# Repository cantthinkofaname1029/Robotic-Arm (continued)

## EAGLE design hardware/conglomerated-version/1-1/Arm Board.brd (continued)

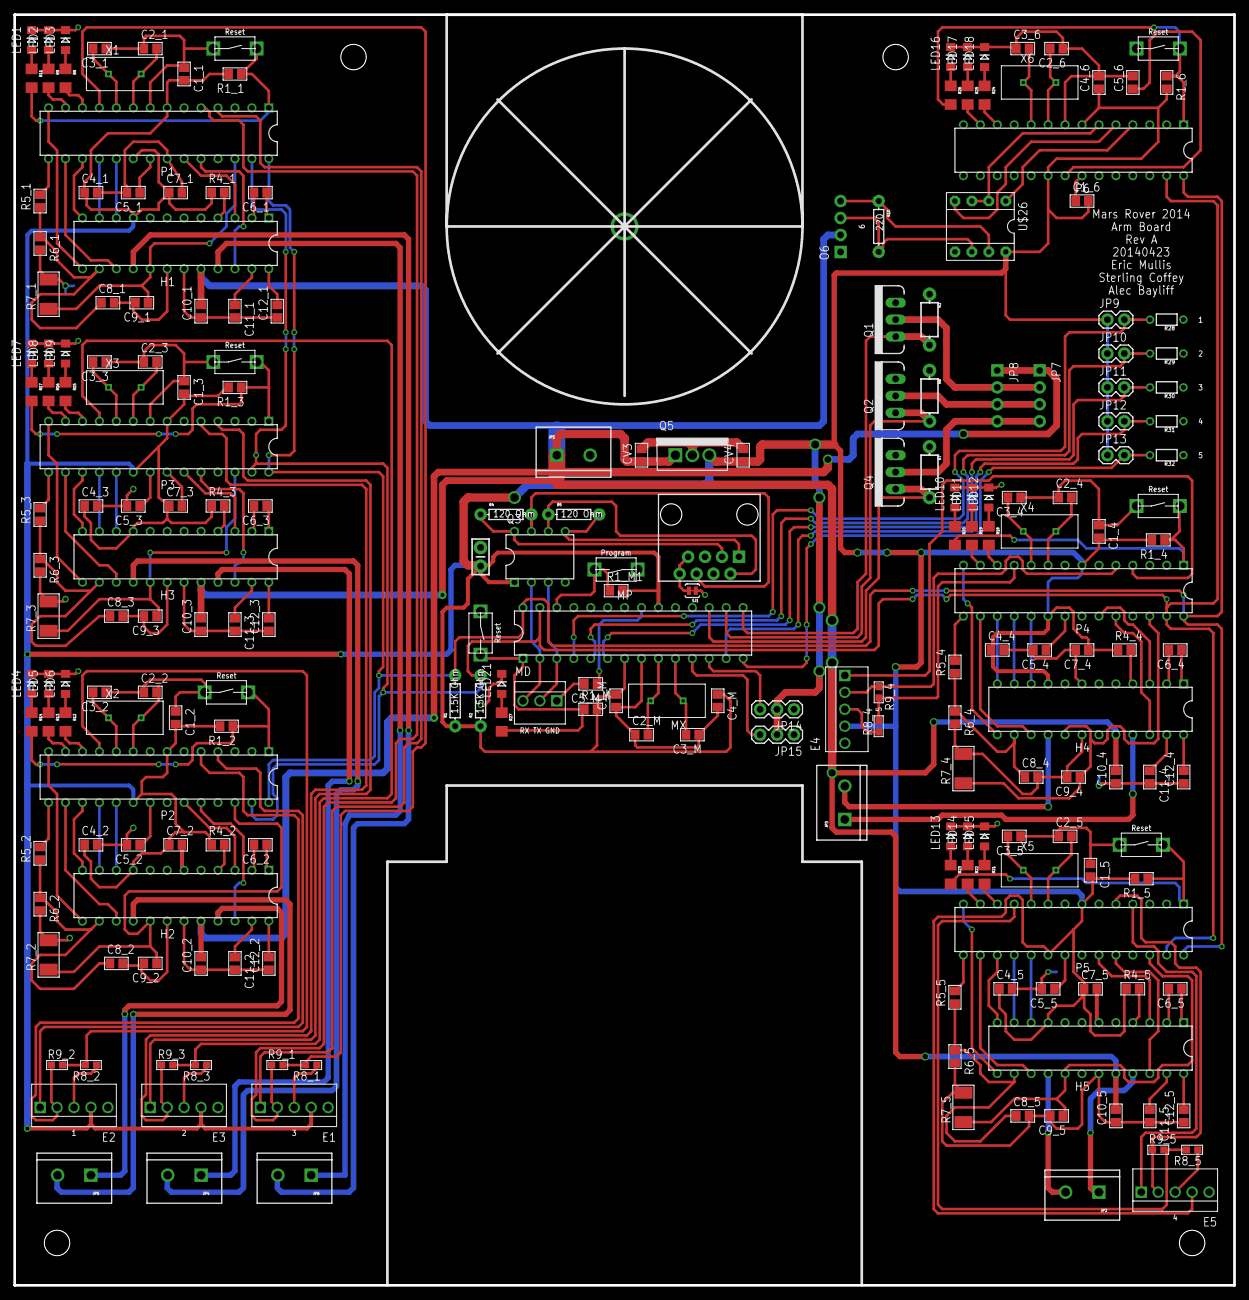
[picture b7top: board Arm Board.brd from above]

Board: 2 copper layers, 182.9 x 190.5 mm, 219 parts (0 on the bottom side), 195 nets.

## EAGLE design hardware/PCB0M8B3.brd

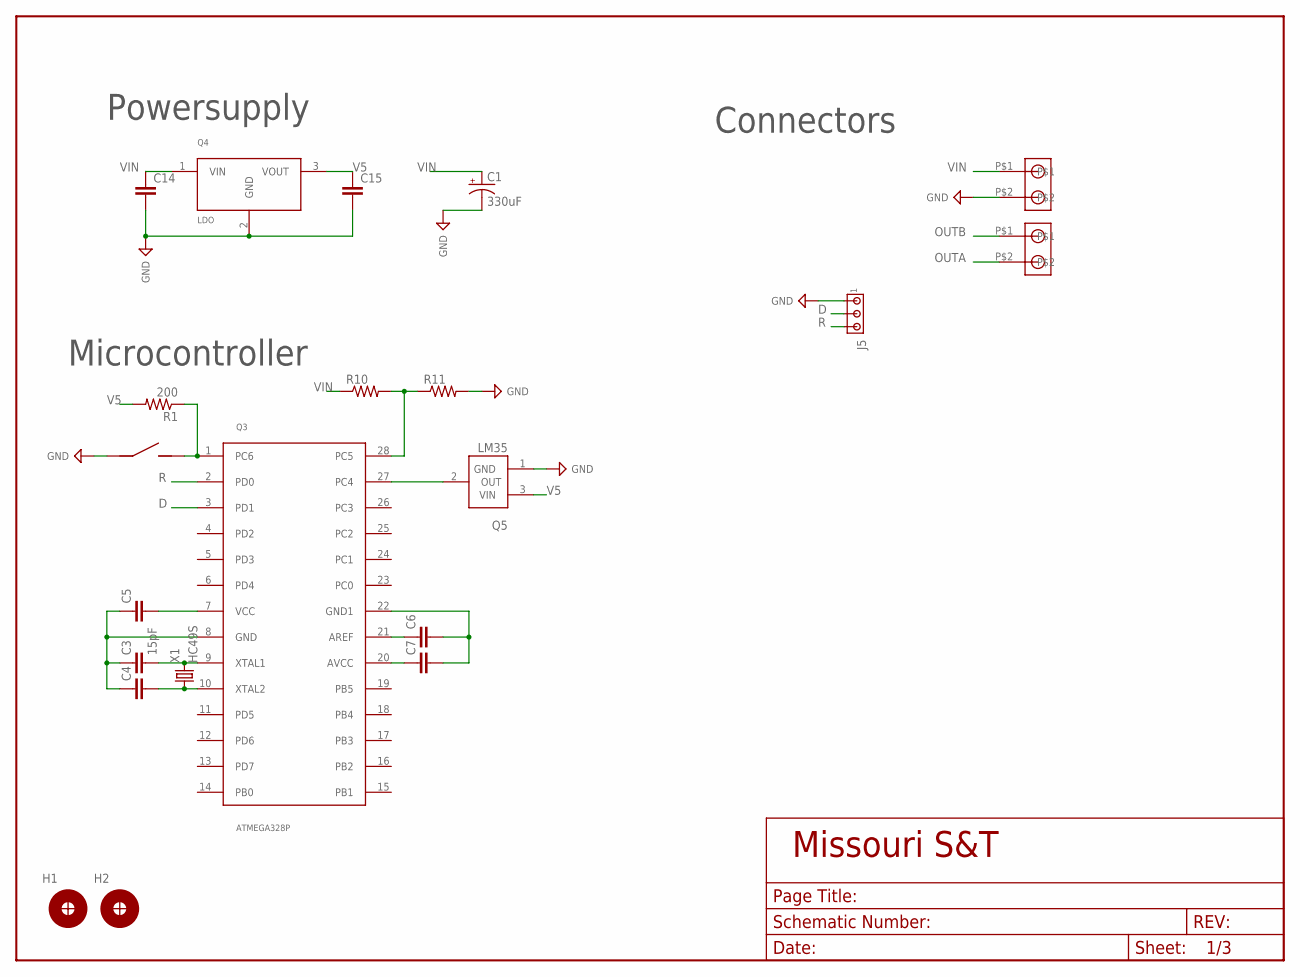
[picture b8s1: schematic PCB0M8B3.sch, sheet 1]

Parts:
C1: 330uF; C_8MM
C3: 15pF; C_0805
C4, C5, C6, C7, C14, C15: C_CAP_0805; C_0805
H1, H2: H_MNTHOLE_#4
J1, J2: J_1546074-2282834-2; J_2.54MM
J4: J_MC32857; J_TOGGLE
J5: J_MTA3P_100; J_MTA100_3P
Q3: ATMEGA328P; DIP28
Q4: LDO; TO-220
Q5: LM35; TO-92-3
R1: 200; R_0805
R10, R11: R_RES_0805; R_0805
X1: HC49S; HC-49

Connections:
D: J5.2, Q3.3 (PD1)
GND: C1.-, C3.1, C4.1, C5.1, C6.2, C7.2, C14.2, C15.2, J1.P$2, J4.P$1 (1), J5.1, Q3.8 (GND), Q3.22 (GND1), Q4.2 (GND), Q5.1 (GND), R11.2; also elsewhere on the board
unnamed: C4.2, Q3.10 (XTAL2), X1.P$1 (1)
unnamed: C3.2, Q3.9 (XTAL1), X1.P$2 (2)
unnamed: Q3.27 (PC4), Q5.2 (OUT)
unnamed: Q3.28 (PC5), R10.2, R11.1
unnamed: C6.1, Q3.21 (AREF)
unnamed: J4.P$2 (2), Q3.1 (PC6), R1.1
OUTA: J2.P$2
OUTB: J2.P$1; also elsewhere on the board
R: J5.3, Q3.2 (PD0)
V5: C5.2, C7.1, C15.1, Q3.7 (VCC), Q3.20 (AVCC), Q4.3 (VOUT), Q5.3 (VIN), R1.2; also elsewhere on the board
VIN: C1.+, C14.1, J1.P$1, Q4.1 (VIN), R10.1; also elsewhere on the board

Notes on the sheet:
Powersupply
Connectors
Microcontroller

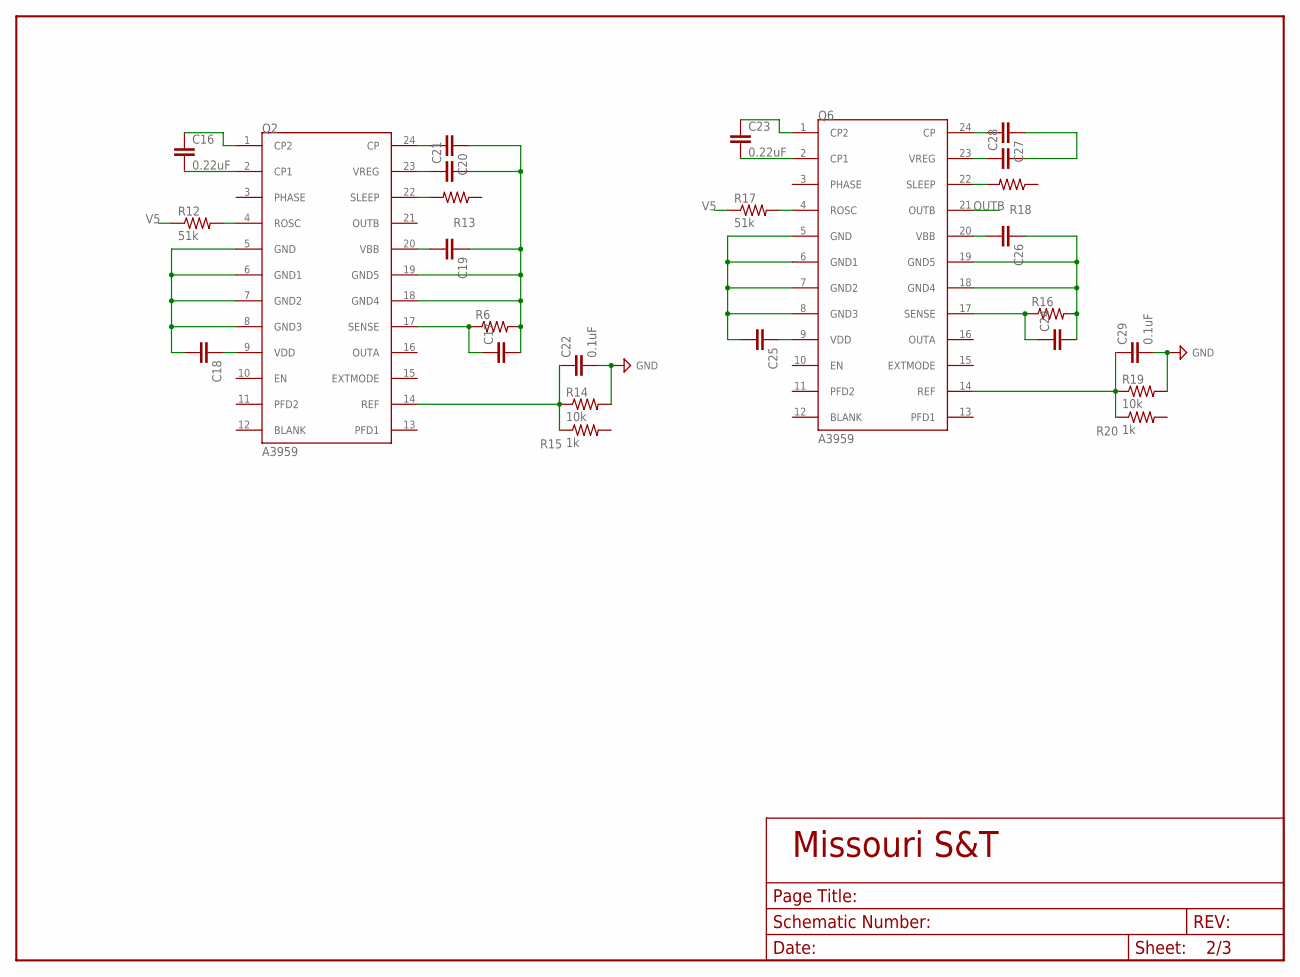
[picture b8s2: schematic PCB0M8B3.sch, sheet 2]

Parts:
C16, C23: 0.22uF; C_0805
C17, C18, C19, C20, C21, C24, C25, C26, C27, C28: C_CAP_0805; C_0805
C22, C29: 0.1uF; C_0805
Q2, Q6: A3959; DIP24
R6, R16: R_RES_2010; R_2010
R12, R17: 51k; R_0805
R13, R18: R_1/4WL
R14, R19: 10k; R_0805
R15, R20: 1k; R_0805

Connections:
GND: C17.2, C18.2, C19.1, C20.1, C21.2, C22.2, C24.2, C25.2, C26.1, C29.2, Q2.5 (GND), Q2.6 (GND1), Q2.7 (GND2), Q2.8 (GND3), Q2.18 (GND4), Q2.19 (GND5), Q6.5 (GND), Q6.6 (GND1), Q6.7 (GND2), Q6.8 (GND3), Q6.18 (GND4), Q6.19 (GND5), R6.2, R14.2, R16.2, R19.2; also elsewhere on the board
ISENSE: C17.1, C24.1, Q2.17 (SENSE), Q6.17 (SENSE), R6.1, R16.1
unnamed: C16.1, Q2.1 (CP2)
unnamed: C16.2, Q2.2 (CP1)
unnamed: Q2.4 (ROSC), R12.2
unnamed: C20.2, Q2.24 (CP)
unnamed: C21.1, Q2.23 (VREG)
unnamed: Q2.22 (SLEEP), R13.2
unnamed: C23.1, Q6.1 (CP2)
unnamed: C23.2, Q6.2 (CP1)
unnamed: Q6.4 (ROSC), R17.2
unnamed: C27.2, Q6.24 (CP)
unnamed: C28.1, Q6.23 (VREG)
unnamed: Q6.22 (SLEEP), R18.2
unnamed: C27.1, C28.2
OUTB: Q6.21 (OUTB); also elsewhere on the board
REF2: C22.1, Q2.14 (REF), R14.1, R15.1
REF3: C29.1, Q6.14 (REF), R19.1, R20.1
V5: C18.1, C25.1, Q2.9 (VDD), Q6.9 (VDD), R12.1, R17.1; also elsewhere on the board
VIN: C19.2, C26.2, Q2.20 (VBB), Q6.20 (VBB); also elsewhere on the board

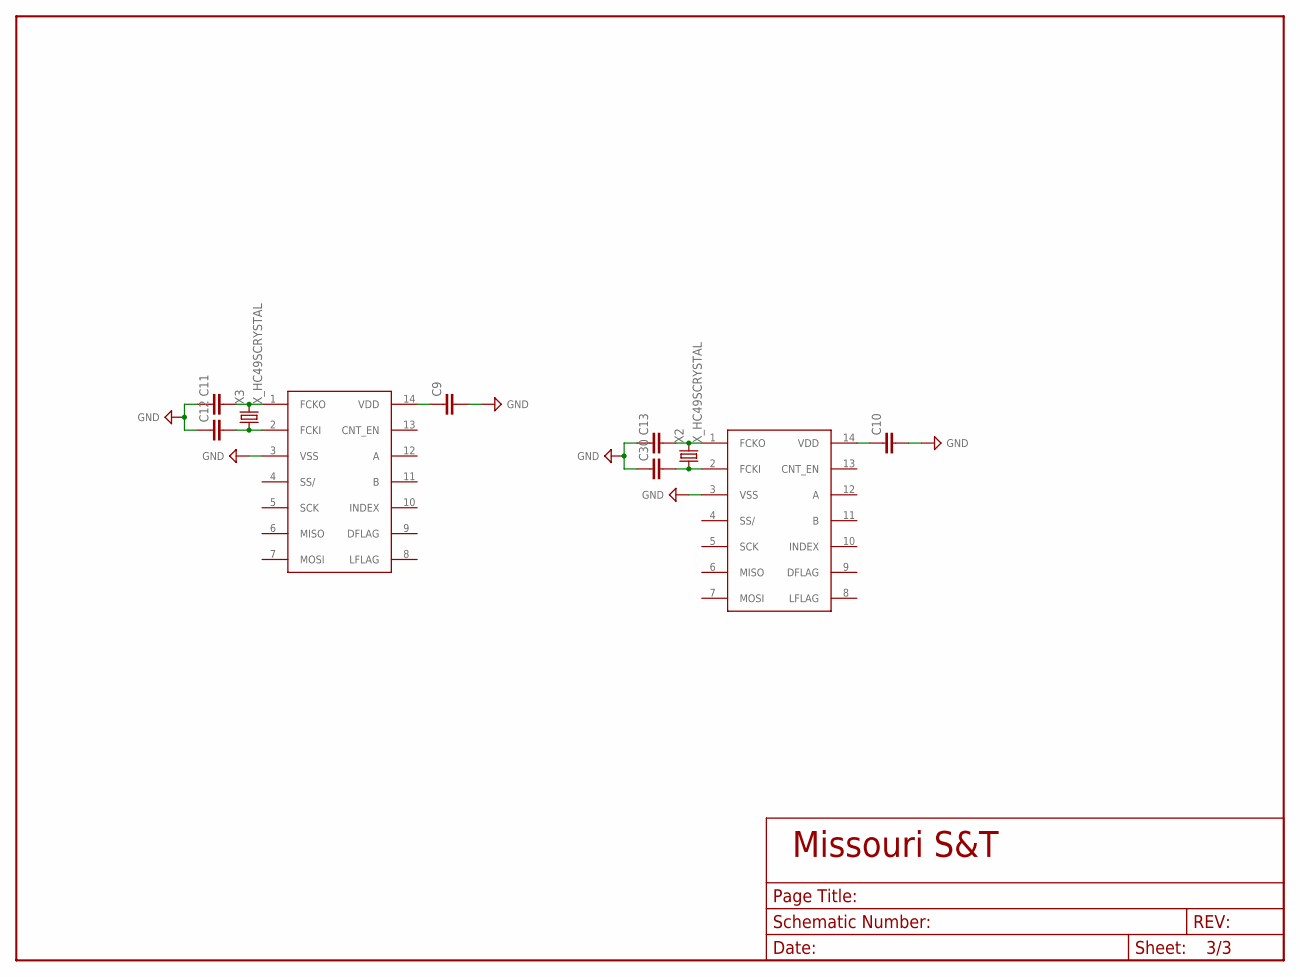
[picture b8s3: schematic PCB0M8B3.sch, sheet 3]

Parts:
C9: C_CAP_1206; C_1206
C10, C11, C12, C13, C30: C_CAP_0805; C_0805
Q8, Q9: Q_LFLS7366R-S; SOIC14
X2, X3: X_HC49SCRYSTAL; HC-49

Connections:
GND: C9.2, C10.2, C11.1, C12.1, C13.1, C30.1, Q8.3 (VSS), Q9.3 (VSS); also elsewhere on the board
unnamed: C9.1, Q8.14 (VDD)
unnamed: C10.1, Q9.14 (VDD)
unnamed: C12.2, Q8.2 (FCKI), X3.P$1 (1)
unnamed: C11.2, Q8.1 (FCKO), X3.P$2 (2)
unnamed: C13.2, Q9.1 (FCKO), X2.P$2 (2)
unnamed: C30.2, Q9.2 (FCKI), X2.P$1 (1)

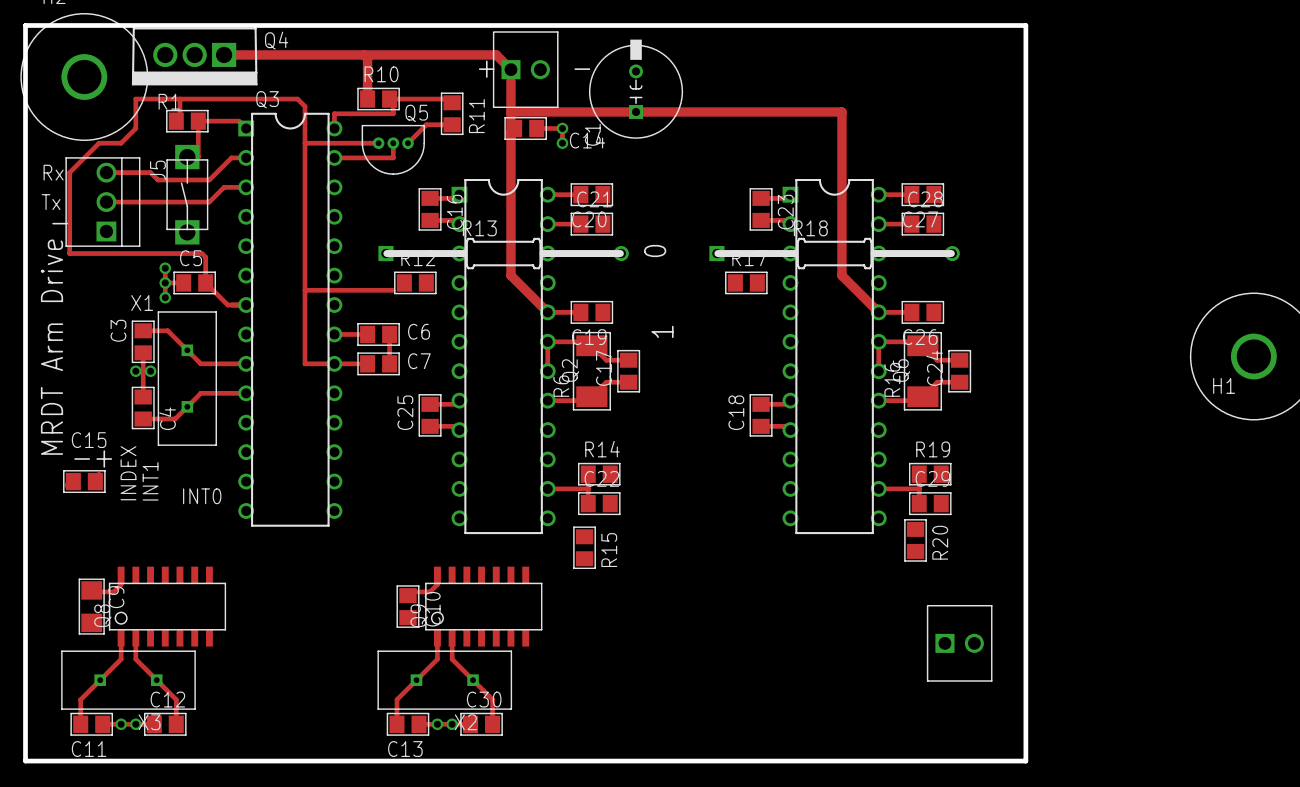
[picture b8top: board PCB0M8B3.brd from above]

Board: 2 copper layers, 86.4 x 63.5 mm, 57 parts (0 on the bottom side), 34 nets.

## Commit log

2014-04-06 Added gitignore and hardware files
2014-04-06 Added files used for manufacturing
2014-04-06 Added datasheet for the PWM based motor driver
2014-04-28 Conglomerated all arm hardware into single board
2014-04-29 Updated board. Updated master to control software to use software UARTs to communicate with slaves
2014-04-30 Debug-printing function works for normal USB serial mode
2014-04-30 Started adding EasyTransfer code
2014-05-02 Added supporting software for base servo
2014-05-02 Added example
2014-05-03 Addition of receive serialization in progress
2014-05-03 More initialization code for struct serialization. Replace Arduino IDE Software Serial libraries with the included ones
2014-05-03 Updated readme to include information about the SoftwareSerial library change
2014-05-03 Stupid file structure changes to fix issues with Arduino IDE
2014-05-03 Now handles incoming struct-serial data except for base servo
2014-05-03 Updated master to actually communicate with Dynamixel servo. Now need to change Dynamixel functions to move servo in a non-blocking way
2014-05-04 All joints working from USB port
2014-05-18 Added Eric's v2 software for the conglomerated board. Restructured file organization to reflect versions v1 and v2
2014-05-18 Reorganized arm hardware file structure to reflect versioning
2014-05-18 A few more hardware file restructuring for organizational purposes. Modified ArmMaster struct to use unint8_t type to be more explicit
2014-05-24 Adding the files eric gave me
2014-05-24 Added reset command
2014-05-25 Updated robot arm commands
2014-09-06 Created v3 Folders
    Created v3 folders and added current v3 schematic and board design.
2014-09-06 Expanded board
2014-09-06 XBEE
2014-09-07 stuff
    Expanded the board
    Binded EA pin to PWMs
2014-09-07 Connected motor controllers and Dynamixel
    Bunch of stuff in the schematic
2014-09-07 Added Xbee connections to schematic
2014-09-08 Removed old board file and created a new one
    Removed the old board file since there were problems with it from
    copying in the Due. This will also allow us to lay it out logically
    with all of the parts on the board.
2014-09-08 Added Launchpad Files
2014-09-08 Added Launchpad to Board
    This included adding it to the schematic, widening the board, and
    placing components.
2014-09-08 Moved old version of board to a folder
2014-09-08 Started routing and added RJ-45
2014-09-09 Started assigning serial pins and routing
    Also added picture of TI Launchpad pinout (It will be fun when it comes
    time to add encoders)
2014-09-09 Added enable pins to schematic and routed
2014-09-09 Did some more routing on the board
2014-09-09 Moved a few things around
2014-09-10 Redid Xbee as well as moved things around
2014-09-10 Changed some stuff on launchpad
2014-09-11 Routed stuffs and stuffs and moved stuff and stuffs
2014-09-12 Routing and Voltage Regulators (See Notes)
    Started to route all of the pins towards the processor. They need to be
    reordered/reassigned since they do not make routing sense. Added the
    +12V and +18V regulators and hooked them up. The +3V3 and +5V still
    need to be picked and placed.
2014-09-12 Stuff
2014-09-12 3V3 Vreg
2014-09-12 5v and 3v3 power rails
    Added a second 12v regulator to drive the 5v and 3v3 regulator
2014-09-13 Finished Routing Data Lines
2014-09-13 Did some clean up
2014-09-13 More Clean Up
2014-09-15 Changed name on l6208 to l6206
2014-09-15 Moved Data Lines closer together
2014-09-15 Finished assigning values and fixing errors
2014-09-15 This finishes the schematic and closes #2
2014-09-15 Created and populated BOM
2014-09-16 Made some traces bigger
2014-09-16 Added RS485 jack next to Xbee
2014-09-16 Added headers for serial in and 2 encoders
2014-09-16 Cleaned up and made sure it complied with 4pcb DRU
2014-09-17 More Cleanup
2014-09-17 Even more cleanup
2014-09-17 Finished cleanup
    Now Alec needs to verify it all
2014-09-17 This finishes the board design and closes #3
2014-09-17 Added labels to outputs and LDOs
2014-09-21 Completed the new Sample End Effecter
2014-09-22 Added Dynamixel Servo Files
2014-09-22 Added BOM and closes #12
2014-09-22 Finished sample end effecter and closes #4
2014-10-27 demo
2014-10-27 added "blah"
2014-10-27 removed demo file
2014-10-27 Started V4
    Started V4
2014-10-27 Continued work on V4
    Started to route power and fixed inconsistency
2014-10-27 Router power and data lines and assigned pins
    Started to route more of the data lines to where they will go. As well
    as working on assigning pins to components.
2014-10-27 mn vc,m
    nbmnb m
2014-10-28 Added a few things and cleaned up some stuff
    Added a few things from last night but mostly cleaning up traces and
    adding parts to it. Commit message last night was by Seto so ignore the
    message.
2014-11-04 A lot of updates getting close to a final board
    Did a lot of changes that got the board closer to the final version.
    Skipped a lot of commits because who cares and github was not getting
    along with me.
2014-11-04 No significant changes
    No significant changes
2014-11-04 Pour and Spacing changes
    Worked on spacing the pours and power connectors so they made sense for
    pluggable screw terminals.
2014-11-04 Folder organization
    Folder organization
2014-11-04 Added a few capacitors
    Added capacitors on voltage supplies and regulator.
2014-11-04 Nothing significant
    Nothing significant
2014-11-05 Nothing Significant again
    Nothing Significant again
2014-11-07 Just a few things with rearranging components
    Moved some power connectors and a few pours
2014-11-09 Seeing how small it can go
    It does not really work well but can be evaluated
2014-11-10 Added Ports file for V3 board
2014-11-11 Nothing much
    Nothing much
2014-11-11 A few little things to do on full Eagle
2014-11-12 Implemented PoRN and Switched Power Connectors
    Implemented PoRN(PoRC) and switched to 3.5mm screw terminals
2014-11-12 Shaved off 1/2 inch for fun
2014-11-13 A few small spacing changes
2014-11-14 Added Stellaris Porting Files
    Added files for the Stellaris port of the old arm code for CCS. Not
    currently finished, needs to have updated ports and probably more
    debugging and other software features for new features on the board.
2014-11-15 Moving things to make room for motor controller
2014-11-15 More stuff
2014-11-15 Added motor controller and cleaned it up
2014-11-15 Clean up. Clean up. Clean up everywhere!
2014-11-17 A few finishing things
2014-11-17 Readded the schematic which somehow got deleted
2014-11-17 A few things
2014-11-18 Replaced caps on voltage regulator
    Need to be moved into place on full eagle and cleaned up a little. But
    replaced them with ones that can be purchased rather then imaginary
    ones I wished existed.
2014-11-18 Added 1uF ceramic caps to help with ripple
2014-11-18 Positioned all the caps correctly
    I think the board is finished but may change as I look for parts to make
    sure everything is correct
2014-11-18 Cleaned up the part names
2014-11-19 Added Mars Rover Bit Mip
2014-11-19 Added a few other boards to work on
2014-11-19 32u4 Xbee Shield
    32u4 Xbee Shield
2014-11-19 Cleaned up and changed a few things on arm
2014-11-19 Moved things around on xbee shield
2014-11-19 Power on the xbee shield
2014-11-20 Added headers for IMU breakout
    In addition to keeping the IMU chip on the board.
2014-11-21 Start of changes for Nathan
2014-11-21 Finished Version 4 of the board
2014-12-10 attempts to convert main.c
    My current attempts at trying to convert the arm's main program for the
    launchpad
2014-12-10 Revert "attempts to convert main.c"
    This reverts commit e1169ea3f4e11665439acfc8d82a64300104bce4.
2014-12-10 (in progress) arm program, board V3
2014-12-10 Ported arduino code to stellaris
2014-12-11 GPIO Setup
    Added Gpio setup and protocols for pinout.
2014-12-11 GPIO Setup
    We initiated the GPIO setup and transfer protocal for pinouts.
2014-12-11 32u4 Shield
2014-12-11 Few more things with shield
2014-12-12 Finished gripper shield
2014-12-13 Near finished Code for Robotic Arm
    We was able to build the code without errors for the dynamixels for the
    Robotic Arm.
2014-12-17 Fixed a few things on shields
2014-12-29 Finished shields for aux
2015-01-12 Revert "Near finished Code for Robotic Arm"
    This reverts commit c79e70b838ebad85c01b88856354583d33e78064.
2015-01-12 Revert "Revert "Near finished Code for Robotic Arm""
    This reverts commit ab0c4457a740263579987729d9b1f28ad8562e1e.
2015-01-12 Revert "Revert "Revert "Near finished Code for Robotic Arm"""
    This reverts commit 966fc79ac9e8e57bb9d128f49c2db74a6339a06e.
2015-01-15 Deleting pdf
